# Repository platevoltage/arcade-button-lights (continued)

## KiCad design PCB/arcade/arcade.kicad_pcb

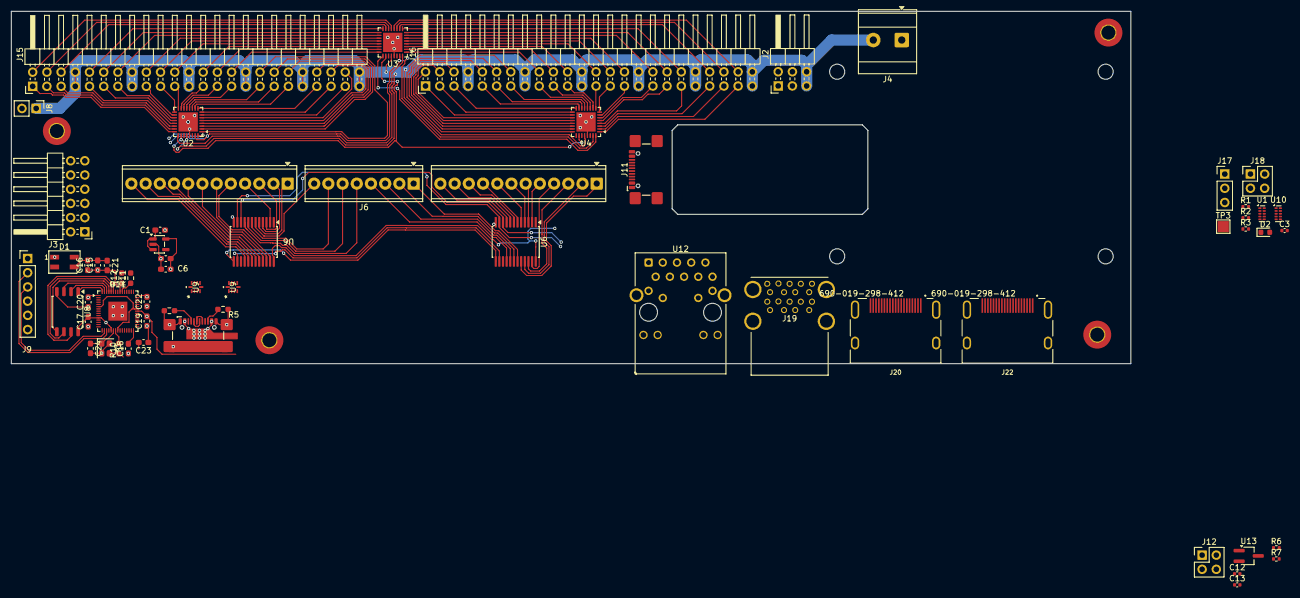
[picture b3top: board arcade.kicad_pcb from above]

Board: 4 copper layers, 200.1 x 63.0 mm, 67 parts (1 on the bottom side), 205 nets.

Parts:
C1, C2: 10uf; C_0603_1608Metric_Pad1.08x0.95mm_HandSolder
C3, C12, C13: 100n; C_0402_1005Metric
C6, C15, C17, C18, C19, C20, C21, C22, C23, C24: 100nf; C_0603_1608Metric_Pad1.08x0.95mm_HandSolder
C16: 2.2uf; C_0603_1608Metric_Pad1.08x0.95mm_HandSolder
D1: SK6812MINI-E; LED_SK6812MINI_PLCC4_3.5x3.5mm_P1.75mm
D2: LED Green; LED_0603_1608Metric
H1, H2, H3, H4: MountingHole; MountingHole_2.5mm_Pad_TopBottom
J1, J11: USB_C_Receptacle_USB2.0_16P; USB_C_Receptacle_GCT_USB4110
J2: Conn_02x03_Odd_Even; PinHeader_2x03_P2.54mm_Horizontal
J3: Conn_02x06_Odd_Even; PinHeader_2x06_P2.54mm_Horizontal
J4: Screw_Terminal_01x02; TerminalBlock_Phoenix_MKDS-3-2-5.08_1x02_P5.08mm_Horizontal
J5, J7: Screw_Terminal_01x12; TerminalBlock_Phoenix_MPT-0,5-12-2.54_1x12_P2.54mm_Horizont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
J6: Screw_Terminal_01x08; TerminalBlock_Phoenix_MPT-0,5-8-2.54_1x08_P2.54mm_Horizontal
J8: Conn_01x02_Pin; PinHeader_1x02_P2.54mm_Vertical
J9: Conn_01x06_Pin; PinHeader_1x06_P2.54mm_Vertical
J12, J18: THD-02-R; PinHeader_2x02_P2.54mm_Vertical
J15, J16: Conn_02x24_Odd_Even; PinHeader_2x24_P2.54mm_Horizontal
J17: Conn_01x03; PinHeader_1x03_P2.54mm_Vertical
J19: USB3_A; MTCONN_UBAF30-D2011
J20, J22: 690-019-298-412; EDAC 690-019-298-412
Module1: ComputeModule5-CM5; Raspberry-Pi-5-Compute-Module
R1: 1k; R_0402_1005Metric
R2, R3: 470R; R_0402_1005Metric
R4, R5, R10: 5.1k; R_0603_1608Metric_Pad0.98x0.95mm_HandSolder
R6, R7: 2.2K 1%; R_0402_1005Metric
R11, R12: 27; R_0603_1608Metric_Pad0.98x0.95mm_HandSolder
TP3: TestPoint; TestPoint_Pad_2.0x2.0mm
U1, U10: TPD4EUSB30; USON-10_2.5x1.0mm_P0.5mm
U2, U3, U4: TLC5947RHB; QFN-32-1EP_5x5mm_P0.5mm_EP3.45x3.45mm
U5: ME6211C33M5; SOT-23-5
U6, U7: CD74HC4067M; SSOP-24_5.3x8.2mm_P0.65mm
U8: W25Q16JVSS; SOIC-8_5.3x5.3mm_P1.27mm
U9, U9#2: TS3USB221ARSERG4; RSE10
U11: RP2350A; QFN-60-1EP_7x7mm_P0.4mm_EP3.4x3.4mm
U12: MagJack-A70-112-331N126; TRJG0926HENL
U13: RT9742SNGV; TSOT-23_HandSoldering
Y3: Crystal_GND24; Crystal_SMD_2520-4Pin_2.5x2.0mm

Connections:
/3.3v: C2.1, C6.1, C15.1, C16.1, C17.2, C18.2, C19.2, C20.2, C21.2, C22.2, J3.9, J3.10, U5.5 (V_{OUT}), U6.24 (VCC), U7.24 (VCC), U8.8 (VCC), U11.1 (IOVDD), U11.11 (IOVDD), U11.20 (IOVDD), U11.30 (IOVDD), U11.38 (IOVDD), U11.45 (IOVDD)
/+1.8v: Module1.88 (+1.8v_(Output)), Module1.90 (+1.8v_(Output))
/+3.3v: D2.2 (A), Module1.84 (+3.3v_(Output)), Module1.86 (+3.3v_(Output)), U12.15 (LEDY_A), U12.17 (LEDG_A)
/+5v: C12.1, Module1.77 (+5v_(Input)), Module1.79 (+5v_(Input)), Module1.81 (+5v_(Input)), Module1.83 (+5v_(Input)), Module1.85 (+5v_(Input)), Module1.87 (+5v_(Input)), U13.1 (IN)
/BT_nDis: J17.3, Module1.91 (BT_nDisable)
/DU+: J1.A6 (D+), J1.B6 (D+)
/DU-: J1.A7 (D-), J1.B7 (D-)
/ETH_LEDG: Module1.17 (Ethernet_nLED2(3.3v)), R2.2
/ETH_LEDY: Module1.15 (Ethernet_nLED3(3.3v)), R3.2
/EXT_5V: J2.5, J2.6, J4.2, J8.1, J15.7, J15.8, J15.15, J15.16, J15.23, J15.24, J15.31, J15.32, J15.39, J15.40, J15.47, J15.48, J16.7, J16.8, J16.15, J16.16, J16.23, J16.24, J16.31, J16.32, J16.39, J16.40, J16.47, J16.48, U2.28 (VCC), U3.28 (VCC), U4.28 (VCC)
/GPIO_VREF: Module1.78 (GPIO_VREF(1.8v/3.3v_Input)), R6.1, R7.1
/HDMI0_CEC: J22.13 (CEC), Module1.151 (HDMI0_CEC)
/HDMI0_CK_N: J22.12 (CK-), Module1.190 (HDMI0_CLK_N)
/HDMI0_CK_P: J22.10 (CK+), Module1.188 (HDMI0_CLK_P)
/HDMI0_D0_N: J22.9 (D0-), Module1.184 (HDMI0_TX0_N)
/HDMI0_D0_P: J22.7 (D0+), Module1.182 (HDMI0_TX0_P)
/HDMI0_D1_N: J22.6 (D1-), Module1.178 (HDMI0_TX1_N)
/HDMI0_D1_P: J22.4 (D1+), Module1.176 (HDMI0_TX1_P)
/HDMI0_D2_N: J22.3 (D2-), Module1.172 (HDMI0_TX2_N)
/HDMI0_D2_P: J22.1 (D2+), Module1.170 (HDMI0_TX2_P)
/HDMI0_HOTPLUG: J22.19 (HPD/HEAC-), Module1.153 (HDMI0_HOTPLUG)
/HDMI0_SCL: J22.15 (SCL), Module1.200 (HDMI0_SCL)
/HDMI0_SDA: J22.16 (SDA), Module1.199 (HDMI0_SDA)
/HDMI1_CEC: J20.13 (CEC), Module1.149 (HDMI1_CEC)
/HDMI1_CK_N: J20.12 (CK-), Module1.166 (HDMI1_CLK_N)
/HDMI1_CK_P: J20.10 (CK+), Module1.164 (HDMI1_CLK_P)
/HDMI1_D0_N: J20.9 (D0-), Module1.160 (HDMI1_TX0_N)
/HDMI1_D0_P: J20.7 (D0+), Module1.158 (HDMI1_TX0_P)
/HDMI1_D1_N: J20.6 (D1-), Module1.154 (HDMI1_TX1_N)
/HDMI1_D1_P: J20.4 (D1+), Module1.152 (HDMI1_TX1_P)
/HDMI1_D2_N: J20.3 (D2-), Module1.148 (HDMI1_TX2_N)
/HDMI1_D2_P: J20.1 (D2+), Module1.146 (HDMI1_TX2_P)
/HDMI1_HOTPLUG: J20.19 (HPD/HEAC-), Module1.143 (HDMI1_HOTPLUG)
/HDMI1_SCL: J20.15 (SCL), Module1.147 (HDMI1_SCL)
/HDMI1_SDA: J20.16 (SDA), Module1.145 (HDMI1_SDA)
/HDMI_5v: C13.1, J20.18 (+5V), J22.18 (+5V), U13.2 (OUT)
/ID_SC: J12.1, Module1.35 (ID_SC)
/ID_SD: J12.3, Module1.36 (ID_SD)
/IO40: U2.26 (XLAT), U3.26 (XLAT), U4.26 (XLAT)
/IO41: U2.31 (SCLK), U3.31 (SCLK), U4.31 (SCLK)
/MISO: J3.3, J3.4
/MOSI: J3.5, J3.6
/PD0: U6.10 (S0), U7.10 (S0)
/PD1: U6.11 (S1), U7.11 (S1)
/PD4: U6.14 (S2), U7.14 (S2)
/PD6: U6.13 (S3), U7.13 (S3)
/QSPI_SCLK: U8.6 (CLK), U11.56 (QSPI_SCLK)
/QSPI_SD0: U8.5 (DI/IO_{0}), U11.57 (QSPI_SD0)
/QSPI_SD1: U8.2 (DO/IO_{1}), U11.59 (QSPI_SD1)
/QSPI_SD2: U8.3 (~WP/IO_{2}), U11.58 (QSPI_SD2)
/QSPI_SD3: U8.7 (~HOLD/~RESET/IO_{3}), U11.55 (QSPI_SD3)
/QSPI_SS: U8.1 (~CS), U11.60 (~QSPI_SS)
/RX0: J9.2, U11.18 (GPIO14)
/SCK: J3.7, J3.8
/SCL1: J12.2, R7.2
/SDA1: J12.4, R6.2
/TR0_TAP: J18.3, U12.11 (VC1)
/TR1_TAP: J18.1, U12.12 (VC2)
/TR2_TAP: J18.2, U12.13 (VC3)
/TR3_TAP: J18.4, U12.14 (VC4)
/TRD0_N: Module1.10 (Ethernet_Pair0_N), U10.4 (D2+), U10.7, U12.2 (TRD0-)
/TRD0_P: Module1.12 (Ethernet_Pair0_P), U10.5 (D2-), U10.6, U12.1 (TRD0+)
/TRD1_N: Module1.6 (Ethernet_Pair1_N), U10.2 (D1-), U10.9, U12.6 (TRD1-)
/TRD1_P: Module1.4 (Ethernet_Pair1_P), U10.1 (D1+), U10.10, U12.3 (TRD1+)
/TRD2_N: Module1.9 (Ethernet_Pair2_N), U1.4 (D2+), U1.7, U12.8 (TRD2-)
/TRD2_P: Module1.11 (Ethernet_Pair2_P), U1.5 (D2-), U1.6, U12.7 (TRD2+)
/TRD3_N: Module1.5 (Ethernet_Pair3_N), U1.2 (D1-), U1.9, U12.10 (TRD3-)
/TRD3_P: Module1.3 (Ethernet_Pair3_P), U1.1 (D1+), U1.10, U12.9 (TRD3+)
/TX0: J9.3, U11.17 (GPIO13)
/USB3-0-D_N: J19.A2 (D-), Module1.136 (USB3-0-D_N)
/USB3-0-D_P: J19.A3 (D+), Module1.134 (USB3-0-D_P)
/USB3-0-RX_N: J19.A6 (SSRX+), Module1.128 (USB3-0-RX_N)
/USB3-0-RX_P: J19.A5 (SSRX-), Module1.130 (USB3-0-RX_P)
/USB3-0-TX_N: J19.A9 (SSTX+), Module1.140 (USB3-0-TX_N)
/USB3-0-TX_P: J19.A8 (SSTX-), Module1.142 (USB3-0-TX_P)
/USB3-1-D_N: J19.B2 (D-), Module1.165 (USB3-1-D_N)
/USB3-1-D_P: J19.B3 (D+), Module1.163 (USB3-1-D_P)
/USB3-1-RX_N: J19.B6 (SSRX+), Module1.157 (USB3-1-RX_N)
/USB3-1-RX_P: J19.B5 (SSRX-), Module1.159 (USB3-1-RX_P)
/USB3-1-TX_N: J19.B9 (SSTX+), Module1.169 (USB3-1-TX_N)
/USB3-1-TX_P: J19.B8 (SSTX-), Module1.171 (USB3-1-TX_P)
/VBUS: C1.1, D1.1 (VSS), J1.A4 (VBUS), J1.A9 (VBUS), J1.B4 (VBUS), J1.B9 (VBUS), J8.2, J9.4, J19.A1 (VBUS), J19.B1 (VBUS), U5.1 (V_{IN}), U5.3 (CE)
/WL_nDis: J17.1, Module1.89 (WiFi_nDisable)
/XIN: C24.1, U11.21 (XIN), Y3.1
/XOUT: R10.2, U11.22 (XOUT)
GND: C1.2, C2.2, C3.2, C6.2, C12.2, C13.2, C15.2, C16.2, C17.1, C18.1, C19.1, C20.1, C21.1, C22.1, C23.1, C24.2, D1.3 (VDD), J1.A1 (GND), J1.A12 (GND), J1.B1 (GND), J1.B12 (GND), J1.S1 (SHIELD), J2.1, J2.2, J3.11, J3.12, J4.1, J9.6, J17.2, J19.10 (SHIELD), J19.A4 (GND), J19.A7 (DRAIN), J19.B4 (GND), J19.B7 (DRAIN), J20.2 (D2S), J20.5 (D1S), J20.8 (D0S), J20.11 (CKS), J20.17 (GND), J20.SH1 (SH), J20.SH2 (SH), J20.SH3 (SH), J20.SH4 (SH), J22.2 (D2S), J22.5 (D1S), J22.8 (D0S), J22.11 (CKS), J22.17 (GND), J22.SH1 (SH), J22.SH2 (SH), J22.SH3 (SH), J22.SH4 (SH), Module1.1 (GND), Module1.2 (GND), Module1.7 (GND), Module1.8 (GND), Module1.13 (GND), Module1.14 (GND), Module1.22 (GND), Module1.23 (GND), Module1.32 (GND), Module1.33 (GND), Module1.42 (GND), Module1.43 (GND), Module1.52 (GND), Module1.53 (GND), Module1.59 (GND), Module1.60 (GND), Module1.65 (GND), Module1.66 (GND), Module1.71 (GND), Module1.74 (GND), Module1.98 (GND), Module1.107 (GND), Module1.108 (GND), Module1.113 (GND), Module1.114 (GND), Module1.119 (GND), Module1.120 (GND), Module1.125 (GND), Module1.126 (GND), Module1.131 (GND), Module1.132 (GND), Module1.137 (GND), Module1.138 (GND), Module1.144 (GND), Module1.150 (GND), Module1.155 (GND), Module1.156 (GND), Module1.161 (GND), Module1.162 (GND), Module1.167 (GND), Module1.168 (GND), Module1.173 (GND), Module1.174 (GND), Module1.179 (GND), Module1.180 (GND), Module1.185 (GND), Module1.186 (GND), Module1.191 (GND), Module1.192 (GND), Module1.197 (GND), Module1.198 (GND), R4.2, R5.2, U1.3 (GND), U1.8 (GND), U2.29 (GND), U2.33 (PowerPAD), U3.29 (GND), U3.33 (PowerPAD), U4.29 (GND), U4.33 (PowerPAD), U5.2 (V_{SS}), U6.12 (GND), U7.12 (GND), U8.4 (GND), U10.3 (GND), U10.8 (GND), U11.61 (GND), U12.19 (SHIELD), U12.20 (SHIELD), U13.3 (GND), Y3.2, Y3.4
unnamed: C3.1, U12.4 (CT), U12.5 (CT)
unnamed: C23.2, R10.1, Y3.3
unnamed: D2.1 (K), R1.1, TP3.1 (1_1)
unnamed: J1.A5 (CC1), R4.1
unnamed: J1.B5 (CC2), R5.1
unnamed: J5.1, U6.20 (I11)
unnamed: J5.2, U6.21 (I10)
unnamed: J5.3, U6.22 (I9)
unnamed: J5.4, U6.23 (I8)
unnamed: J5.5, U6.2 (I7)
unnamed: J5.6, U6.3 (I6)
unnamed: J5.7, U6.4 (I5)
unnamed: J5.8, U6.5 (I4)
unnamed: J5.9, U6.6 (I3)
unnamed: J5.10, U6.7 (I2)
unnamed: J5.11, U6.8 (I1)
unnamed: J5.12, U6.9 (I0)
unnamed: J6.1, U6.19 (I12)
unnamed: J6.2, U6.18 (I13)
unnamed: J6.3, U6.17 (I14)
unnamed: J6.4, U6.16 (I15)
unnamed: J6.5, U7.9 (I0)
unnamed: J6.6, U7.8 (I1)
unnamed: J6.7, U7.7 (I2)
unnamed: J6.8, U7.6 (I3)
unnamed: J7.1, U7.5 (I4)
unnamed: J7.2, U7.4 (I5)
unnamed: J7.3, U7.3 (I6)
unnamed: J7.4, U7.2 (I7)
unnamed: J7.5, U7.23 (I8)
unnamed: J7.6, U7.22 (I9)
unnamed: J7.7, U7.21 (I10)
unnamed: J7.8, U7.20 (I11)
unnamed: J7.9, U7.19 (I12)
unnamed: J7.10, U7.18 (I13)
unnamed: J7.11, U7.17 (I14)
unnamed: J7.12, U7.16 (I15)
unnamed: J11.A1 (GND), J11.A12 (GND), J11.B1 (GND), J11.B12 (GND)
unnamed: J11.A4 (VBUS), J11.A9 (VBUS), J11.B4 (VBUS), J11.B9 (VBUS)
unnamed: J15.1, U2.24 (OUT23)
unnamed: J15.2, U3.13 (OUT12)
unnamed: J15.3, U2.23 (OUT22)
unnamed: J15.4, U3.14 (OUT13)
unnamed: J15.5, U2.22 (OUT21)
unnamed: J15.6, U3.15 (OUT14)
unnamed: J15.9, U2.21 (OUT20)
unnamed: J15.10, U3.16 (OUT15)
unnamed: J15.11, U2.20 (OUT19)
unnamed: J15.12, U3.17 (OUT16)
unnamed: J15.13, U2.19 (OUT18)
unnamed: J15.14, U3.18 (OUT17)
unnamed: J15.17, U2.18 (OUT17)
unnamed: J15.18, U3.19 (OUT18)
unnamed: J15.19, U2.17 (OUT16)
unnamed: J15.20, U3.20 (OUT19)
unnamed: J15.21, U2.16 (OUT15)
unnamed: J15.22, U3.21 (OUT20)
unnamed: J15.25, U2.15 (OUT14)
unnamed: J15.26, U3.22 (OUT21)
unnamed: J15.27, U2.14 (OUT13)
unnamed: J15.28, U3.23 (OUT22)
unnamed: J15.29, U2.13 (OUT12)
unnamed: J15.30, U3.24 (OUT23)
unnamed: J15.33, U2.12 (OUT11)
unnamed: J15.34, U2.1 (OUT0)
unnamed: J15.35, U2.11 (OUT10)
unnamed: J15.36, U2.2 (OUT1)
unnamed: J15.37, U2.10 (OUT9)
unnamed: J15.38, U2.3 (OUT2)
unnamed: J15.41, U2.9 (OUT8)
unnamed: J15.42, U2.4 (OUT3)
unnamed: J15.43, U2.8 (OUT7)
unnamed: J15.44, U2.5 (OUT4)
unnamed: J15.45, U2.7 (OUT6)
unnamed: J15.46, U2.6 (OUT5)
unnamed: J16.1, U4.18 (OUT17)
unnamed: J16.2, U4.19 (OUT18)
unnamed: J16.3, U4.17 (OUT16)
unnamed: J16.4, U4.20 (OUT19)
unnamed: J16.5, U4.16 (OUT15)
unnamed: J16.6, U4.21 (OUT20)
unnamed: J16.9, U4.15 (OUT14)
unnamed: J16.10, U4.22 (OUT21)
unnamed: J16.11, U4.14 (OUT13)
unnamed: J16.12, U4.23 (OUT22)
unnamed: J16.13, U4.13 (OUT12)
unnamed: J16.14, U4.24 (OUT23)
unnamed: J16.17, U4.12 (OUT11)
unnamed: J16.18, U3.1 (OUT0)
unnamed: J16.19, U4.11 (OUT10)
unnamed: J16.20, U3.2 (OUT1)
unnamed: J16.21, U4.10 (OUT9)
unnamed: J16.22, U3.3 (OUT2)
unnamed: J16.25, U4.9 (OUT8)
unnamed: J16.26, U3.4 (OUT3)
unnamed: J16.27, U4.8 (OUT7)
unnamed: J16.28, U3.5 (OUT4)
unnamed: J16.29, U4.7 (OUT6)
unnamed: J16.30, U3.6 (OUT5)
unnamed: J16.33, U4.6 (OUT5)
unnamed: J16.34, U3.7 (OUT6)
unnamed: J16.35, U4.5 (OUT4)
unnamed: J16.36, U3.8 (OUT7)
unnamed: J16.37, U4.4 (OUT3)
unnamed: J16.38, U3.9 (OUT8)
unnamed: J16.41, U4.3 (OUT2)
unnamed: J16.42, U3.10 (OUT9)
unnamed: J16.43, U4.2 (OUT1)
unnamed: J16.44, U3.11 (OUT10)
unnamed: J16.45, U4.1 (OUT0)
unnamed: J16.46, U3.12 (OUT11)
unnamed: Module1.21 (LED_nACT), R1.2
unnamed: U2.25 (SOUT), U3.32 (SIN)
unnamed: U3.25 (SOUT), U4.32 (SIN)
unnamed: U11.6 (DVDD), U11.23 (DVDD), U11.39 (DVDD)
unnamed: R11.1, U11.51 (USB_DM)
unnamed: R12.1, U11.52 (USB_DP)
unnamed: R3.1, U12.18 (LEDG_K)
unnamed: R2.1, U12.16 (LEDY_K)

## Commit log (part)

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2025-07-21 init
2025-07-21 takes JSON now
2025-07-23 refactor
2025-07-23 added buttons
2025-07-24 added keyboard control
2025-07-24 async lights
2025-07-24 fade in and out
2025-07-24 fixed heap
2025-07-26 new method of lights
2025-08-01 added player 2 buttons
2025-08-25 updated keyboard
2025-08-30 3d print
2025-10-19 key over serial
2026-04-22 lots of shit
2026-04-26 pins
